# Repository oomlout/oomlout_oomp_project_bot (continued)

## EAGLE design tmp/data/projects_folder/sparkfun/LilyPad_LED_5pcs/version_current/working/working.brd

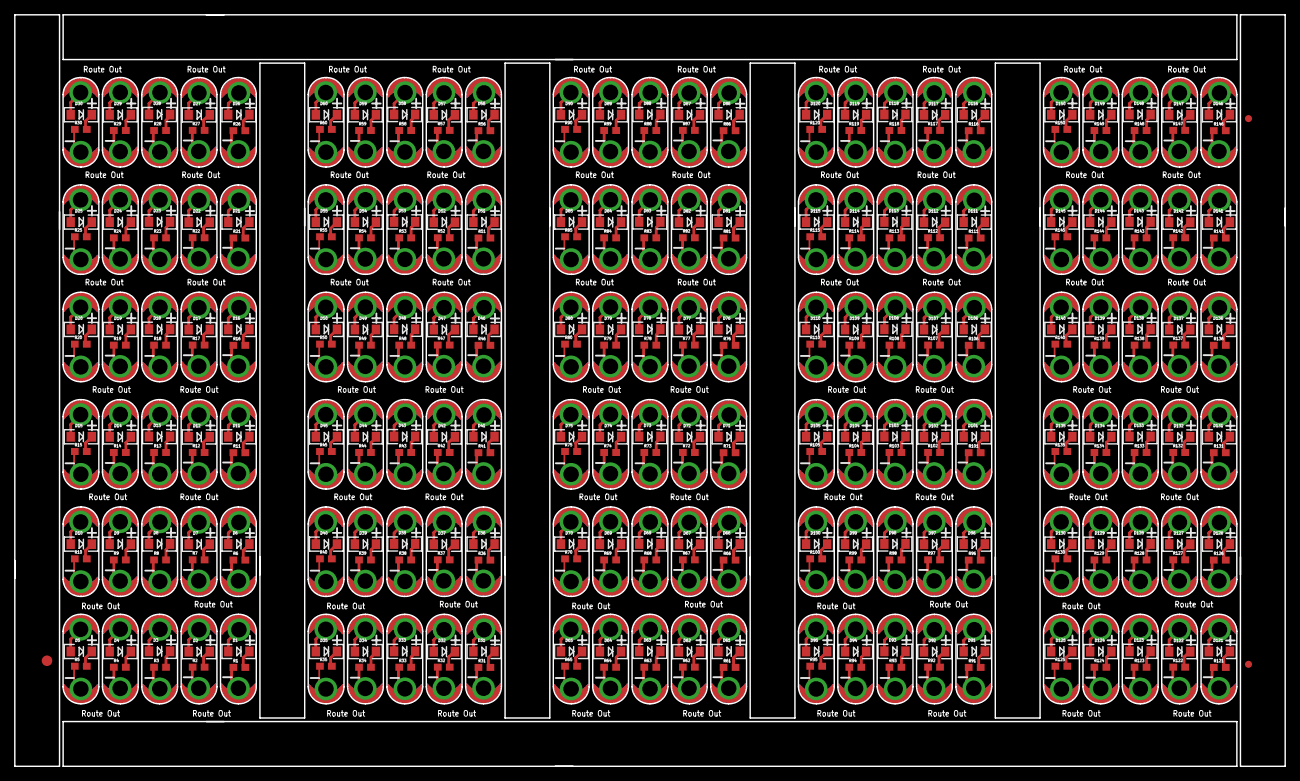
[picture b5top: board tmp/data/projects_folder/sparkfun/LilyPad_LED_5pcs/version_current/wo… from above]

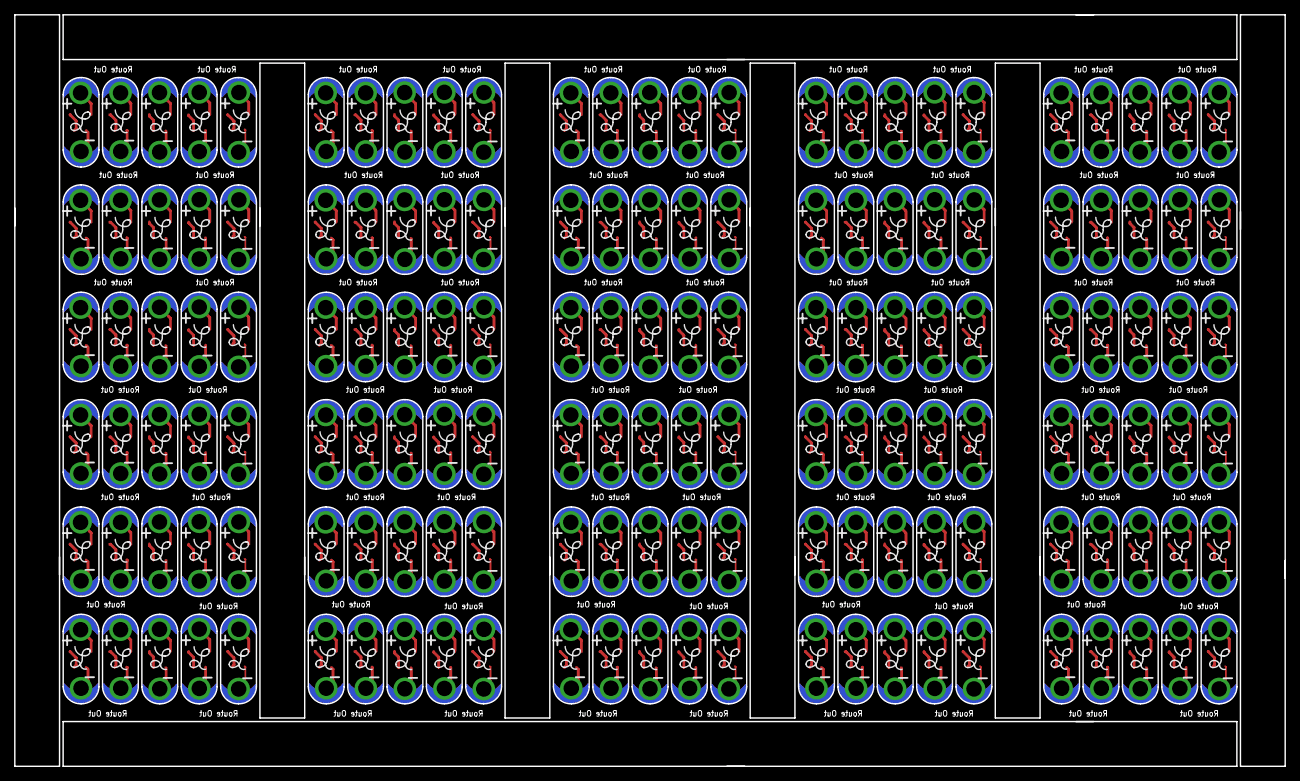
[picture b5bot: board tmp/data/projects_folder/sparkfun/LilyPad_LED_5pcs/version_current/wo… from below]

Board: 2 copper layers, 180.3 x 106.7 mm, 753 parts (150 on the bottom side), 450 nets.

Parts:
D1, D2, D3, D4, D5, D6, D7, D8, D9, D10, D11, D12, D13, D14, D15, D16, D17, D18, D19, D20, D21, D22, D23, D24, D25, D26, D27, D28, D29, D30, D31, D32, D33, D34, D35, D36, D37, D38, D39, D40, D41, D42, D43, D44, D45, D46, D47, D48, D49, D50, D51, D52, D53, D54, D55, D56, D57, D58, D59, D60, D61, D62, D63, D64, D65, D66, D67, D68, D69, D70, D71, D72, D73, D74, D75, D76, D77, D78, D79, D80, D81, D82, D83, D84, D85, D86, D87, D88, D89, D90, D91, D92, D93, D94, D95, D96, D97, D98, D99, D100, D101, D102, D103, D104, D105, D106, D107, D108, D109, D110, D111, D112, D113, D114, D115, D116, D117, D118, D119, D120, D121, D122, D123, D124, D125, D126, D127, D128, D129, D130, D131, D132, D133, D134, D135, D136, D137, D138, D139, D140, D141, D142, D143, D144, D145, D146, D147, D148, D149, D150: WHITE; LED-1206
E$1: FIDUCIAL-1.5X3
E$15, E$16: FIDUCIAL-1X2
LED+1, LED+2, LED+3, LED+4, LED+5, LED+6, LED+7, LED+8, LED+9, LED+10, LED+11, LED+12, LED+13, LED+14, LED+15, LED+16, LED+17, LED+18, LED+19, LED+20, LED+21, LED+22, LED+23, LED+24, LED+25, LED+26, LED+27, LED+28, LED+29, LED+30, LED+31, LED+32, LED+33, LED+34, LED+35, LED+36, LED+37, LED+38, LED+39, LED+40, LED+41, LED+42, LED+43, LED+44, LED+45, LED+46, LED+47, LED+48, LED+49, LED+50, LED+51, LED+52, LED+53, LED+54, LED+55, LED+56, LED+57, LED+58, LED+59, LED+60, LED+61, LED+62, LED+63, LED+64, LED+65, LED+66, LED+67, LED+68, LED+69, LED+70, LED+71, LED+72, LED+73, LED+74, LED+75, LED+76, LED+77, LED+78, LED+79, LED+80, LED+81, LED+82, LED+83, LED+84, LED+85, LED+86, LED+87, LED+88, LED+89, LED+90, LED+91, LED+92, LED+93, LED+94, LED+95, LED+96, LED+97, LED+98, LED+99, LED+100, LED+101, LED+102, LED+103, LED+104, LED+105, LED+106, LED+107, LED+108, LED+109, LED+110, LED+111, LED+112, LED+113, LED+114, LED+115, LED+116, LED+117, LED+118, LED+119, LED+120, LED+121, LED+122, LED+123, LED+124, LED+125, LED+126, LED+127, LED+128, LED+129, LED+130, LED+131, LED+132, LED+133, LED+134, LED+135, LED+136, LED+137, LED+138, LED+139, LED+140, LED+141, LED+142, LED+143, LED+144, LED+145, LED+146, LED+147, LED+148, LED+149, LED+150: SEWTAP6; PETAL-SMALL-2SIDE
LED-1, LED-2, LED-3, LED-4, LED-5, LED-6, LED-7, LED-8, LED-9, LED-10, LED-11, LED-12, LED-13, LED-14, LED-15, LED-16, LED-17, LED-18, LED-19, LED-20, LED-21, LED-22, LED-23, LED-24, LED-25, LED-26, LED-27, LED-28, LED-29, LED-30, LED-31, LED-32, LED-33, LED-34, LED-35, LED-36, LED-37, LED-38, LED-39, LED-40, LED-41, LED-42, LED-43, LED-44, LED-45, LED-46, LED-47, LED-48, LED-49, LED-50, LED-51, LED-52, LED-53, LED-54, LED-55, LED-56, LED-57, LED-58, LED-59, LED-60, LED-61, LED-62, LED-63, LED-64, LED-65, LED-66, LED-67, LED-68, LED-69, LED-70, LED-71, LED-72, LED-73, LED-74, LED-75, LED-76, LED-77, LED-78, LED-79, LED-80, LED-81, LED-82, LED-83, LED-84, LED-85, LED-86, LED-87, LED-88, LED-89, LED-90, LED-91, LED-92, LED-93, LED-94, LED-95, LED-96, LED-97, LED-98, LED-99, LED-100, LED-101, LED-102, LED-103, LED-104, LED-105, LED-106, LED-107, LED-108, LED-109, LED-110, LED-111, LED-112, LED-113, LED-114, LED-115, LED-116, LED-117, LED-118, LED-119, LED-120, LED-121, LED-122, LED-123, LED-124, LED-125, LED-126, LED-127, LED-128, LED-129, LED-130, LED-131, LED-132, LED-133, LED-134, LED-135, LED-136, LED-137, LED-138, LED-139, LED-140, LED-141, LED-142, LED-143, LED-144, LED-145, LED-146, LED-147, LED-148, LED-149, LED-150: SEWTAP6; PETAL-SMALL-2SIDE
R1, R2, R3, R4, R5, R6, R7, R8, R9, R10, R11, R12, R13, R14, R15, R16, R17, R18, R19, R20, R21, R22, R23, R24, R25, R26, R27, R28, R29, R30, R31, R32, R33, R34, R35, R36, R37, R38, R39, R40, R41, R42, R43, R44, R45, R46, R47, R48, R49, R50, R51, R52, R53, R54, R55, R56, R57, R58, R59, R60, R61, R62, R63, R64, R65, R66, R67, R68, R69, R70, R71, R72, R73, R74, R75, R76, R77, R78, R79, R80, R81, R82, R83, R84, R85, R86, R87, R88, R89, R90, R91, R92, R93, R94, R95, R96, R97, R98, R99, R100, R101, R102, R103, R104, R105, R106, R107, R108, R109, R110, R111, R112, R113, R114, R115, R116, R117, R118, R119, R120, R121, R122, R123, R124, R125, R126, R127, R128, R129, R130, R131, R132, R133, R134, R135, R136, R137, R138, R139, R140, R141, R142, R143, R144, R145, R146, R147, R148, R149, R150: 150; 0603-RES
U$1, U$2, U$3, U$4, U$5, U$6, U$7, U$8, U$9, U$10, U$11, U$12, U$13, U$14, U$15, U$16, U$17, U$18, U$19, U$20, U$21, U$22, U$23, U$24, U$25, U$26, U$27, U$28, U$29, U$30, U$31, U$32, U$33, U$34, U$35, U$36, U$37, U$38, U$39, U$40, U$41, U$42, U$43, U$44, U$45, U$46, U$47, U$48, U$49, U$50, U$51, U$52, U$53, U$54, U$55, U$56, U$57, U$58, U$59, U$60, U$61, U$62, U$63, U$64, U$65, U$66, U$67, U$68, U$69, U$70, U$71, U$72, U$73, U$74, U$75, U$76, U$77, U$78, U$79, U$80, U$81, U$82, U$83, U$84, U$85, U$86, U$87, U$88, U$89, U$90, U$91, U$92, U$93, U$94, U$95, U$96, U$97, U$98, U$99, U$100, U$101, U$102, U$103, U$104, U$105, U$106, U$107, U$108, U$109, U$110, U$111, U$112, U$113, U$114, U$115, U$116, U$117, U$118, U$119, U$120, U$121, U$122, U$123, U$124, U$125, U$126, U$127, U$128, U$129, U$130, U$131, U$132, U$133, U$134, U$135, U$136, U$137, U$138, U$139, U$140, U$141, U$142, U$143, U$144, U$145, U$146, U$147, U$148, U$149, U$150: LOGO-L

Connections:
1: D1.A, LED+1.1
2: D1.C, R1.2
3: LED-1.1, R1.1
4: D2.A, LED+2.1
5: D2.C, R2.2
6: LED-2.1, R2.1
7: D3.A, LED+3.1
8: D3.C, R3.2
9: LED-3.1, R3.1
10: D4.A, LED+4.1
11: D4.C, R4.2
12: LED-4.1, R4.1
13: D5.A, LED+5.1
14: D5.C, R5.2
15: LED-5.1, R5.1
16: LED-6.1, R6.1
17: D6.A, LED+6.1
18: D6.C, R6.2
19: D7.A, LED+7.1
20: D7.C, R7.2
21: LED-7.1, R7.1
22: D8.A, LED+8.1
23: D8.C, R8.2
24: LED-8.1, R8.1
25: LED-9.1, R9.1
26: D9.C, R9.2
27: D9.A, LED+9.1
28: D10.A, LED+10.1
29: D10.C, R10.2
30: LED-10.1, R10.1
31: LED-11.1, R11.1
32: D11.A, LED+11.1
33: D11.C, R11.2
34: D12.A, LED+12.1
35: D12.C, R12.2
36: LED-12.1, R12.1
37: D13.A, LED+13.1
38: D13.C, R13.2
39: LED-13.1, R13.1
40: LED-14.1, R14.1
41: D14.C, R14.2
42: D14.A, LED+14.1
43: D15.A, LED+15.1
44: D15.C, R15.2
45: LED-15.1, R15.1
46: LED-16.1, R16.1
47: D16.A, LED+16.1
48: D16.C, R16.2
49: D17.A, LED+17.1
50: D17.C, R17.2
51: LED-17.1, R17.1
52: D18.A, LED+18.1
53: D18.C, R18.2
54: LED-18.1, R18.1
55: LED-19.1, R19.1
56: D19.C, R19.2
57: D19.A, LED+19.1
58: D20.A, LED+20.1
59: D20.C, R20.2
60: LED-20.1, R20.1
61: LED-21.1, R21.1
62: D21.A, LED+21.1
63: D21.C, R21.2
64: D22.A, LED+22.1
65: D22.C, R22.2
66: LED-22.1, R22.1
67: D23.A, LED+23.1
68: D23.C, R23.2
69: LED-23.1, R23.1
70: LED-24.1, R24.1
71: D24.C, R24.2
72: D24.A, LED+24.1
73: D25.A, LED+25.1
74: D25.C, R25.2
75: LED-25.1, R25.1
76: LED-26.1, R26.1
77: D26.A, LED+26.1
78: D26.C, R26.2
79: D27.A, LED+27.1
80: D27.C, R27.2
81: LED-27.1, R27.1
82: D28.A, LED+28.1
83: D28.C, R28.2
84: LED-28.1, R28.1
85: LED-29.1, R29.1
86: D29.C, R29.2
87: D29.A, LED+29.1
88: D30.A, LED+30.1
89: D30.C, R30.2
90: LED-30.1, R30.1
91: LED-31.1, R31.1
92: D31.A, LED+31.1
93: D31.C, R31.2
94: D32.A, LED+32.1
95: D32.C, R32.2
96: LED-32.1, R32.1
97: D33.A, LED+33.1
98: D33.C, R33.2
99: LED-33.1, R33.1
100: LED-34.1, R34.1
101: D34.C, R34.2
102: D34.A, LED+34.1
103: D35.A, LED+35.1
104: D35.C, R35.2
105: LED-35.1, R35.1
106: LED-36.1, R36.1
107: D36.A, LED+36.1
108: D36.C, R36.2
109: D37.A, LED+37.1
110: D37.C, R37.2
111: LED-37.1, R37.1
112: D38.A, LED+38.1
113: D38.C, R38.2
114: LED-38.1, R38.1
115: LED-39.1, R39.1
116: D39.C, R39.2
117: D39.A, LED+39.1
118: D40.A, LED+40.1
119: D40.C, R40.2
120: LED-40.1, R40.1
121: LED-41.1, R41.1
122: D41.A, LED+41.1
123: D41.C, R41.2
124: D42.A, LED+42.1
125: D42.C, R42.2
126: LED-42.1, R42.1
127: D43.A, LED+43.1
128: D43.C, R43.2
129: LED-43.1, R43.1
130: LED-44.1, R44.1
131: D44.C, R44.2
132: D44.A, LED+44.1
133: D45.A, LED+45.1
134: D45.C, R45.2
135: LED-45.1, R45.1
136: LED-46.1, R46.1
137: D46.A, LED+46.1
138: D46.C, R46.2
139: D47.A, LED+47.1
140: D47.C, R47.2
141: LED-47.1, R47.1
142: D48.A, LED+48.1
143: D48.C, R48.2
144: LED-48.1, R48.1
145: LED-49.1, R49.1
146: D49.C, R49.2
147: D49.A, LED+49.1
148: D50.A, LED+50.1
149: D50.C, R50.2
150: LED-50.1, R50.1
151: LED-51.1, R51.1
152: D51.A, LED+51.1
153: D51.C, R51.2
154: D52.A, LED+52.1
155: D52.C, R52.2
156: LED-52.1, R52.1
157: D53.A, LED+53.1
158: D53.C, R53.2
159: LED-53.1, R53.1
160: LED-54.1, R54.1
161: D54.C, R54.2
162: D54.A, LED+54.1
163: D55.A, LED+55.1
164: D55.C, R55.2
165: LED-55.1, R55.1
166: LED-56.1, R56.1
167: D56.A, LED+56.1
168: D56.C, R56.2
169: D57.A, LED+57.1
170: D57.C, R57.2
171: LED-57.1, R57.1
172: D58.A, LED+58.1
173: D58.C, R58.2
174: LED-58.1, R58.1
175: LED-59.1, R59.1
176: D59.C, R59.2
177: D59.A, LED+59.1
178: D60.A, LED+60.1
179: D60.C, R60.2
180: LED-60.1, R60.1
181: LED-61.1, R61.1
182: D61.A, LED+61.1
183: D61.C, R61.2
184: D62.A, LED+62.1
185: D62.C, R62.2
186: LED-62.1, R62.1
187: D63.A, LED+63.1
188: D63.C, R63.2
189: LED-63.1, R63.1
190: LED-64.1, R64.1
191: D64.C, R64.2
192: D64.A, LED+64.1
193: D65.A, LED+65.1
194: D65.C, R65.2
195: LED-65.1, R65.1
196: LED-66.1, R66.1
197: D66.A, LED+66.1
198: D66.C, R66.2
199: D67.A, LED+67.1
200: D67.C, R67.2
201: LED-67.1, R67.1
202: D68.A, LED+68.1
203: D68.C, R68.2
204: LED-68.1, R68.1
205: LED-69.1, R69.1
206: D69.C, R69.2
207: D69.A, LED+69.1
208: D70.A, LED+70.1
209: D70.C, R70.2
210: LED-70.1, R70.1
211: LED-71.1, R71.1
212: D71.A, LED+71.1
213: D71.C, R71.2
214: D72.A, LED+72.1
215: D72.C, R72.2
216: LED-72.1, R72.1
217: D73.A, LED+73.1
218: D73.C, R73.2
219: LED-73.1, R73.1
220: LED-74.1, R74.1
221: D74.C, R74.2
222: D74.A, LED+74.1
223: D75.A, LED+75.1
224: D75.C, R75.2
225: LED-75.1, R75.1
226: LED-76.1, R76.1
227: D76.A, LED+76.1
228: D76.C, R76.2
229: D77.A, LED+77.1
230: D77.C, R77.2
231: LED-77.1, R77.1
232: D78.A, LED+78.1
233: D78.C, R78.2
234: LED-78.1, R78.1
235: LED-79.1, R79.1
236: D79.C, R79.2
237: D79.A, LED+79.1
238: D80.A, LED+80.1
239: D80.C, R80.2
240: LED-80.1, R80.1
241: LED-81.1, R81.1
242: D81.A, LED+81.1
243: D81.C, R81.2
244: D82.A, LED+82.1
245: D82.C, R82.2
246: LED-82.1, R82.1
247: D83.A, LED+83.1
248: D83.C, R83.2
249: LED-83.1, R83.1
250: LED-84.1, R84.1
251: D84.C, R84.2
252: D84.A, LED+84.1
253: D85.A, LED+85.1
254: D85.C, R85.2
255: LED-85.1, R85.1
256: LED-86.1, R86.1
257: D86.A, LED+86.1
258: D86.C, R86.2
259: D87.A, LED+87.1
260: D87.C, R87.2
261: LED-87.1, R87.1
262: D88.A, LED+88.1
263: D88.C, R88.2
264: LED-88.1, R88.1
265: LED-89.1, R89.1
266: D89.C, R89.2
267: D89.A, LED+89.1
268: D90.A, LED+90.1
269: D90.C, R90.2
270: LED-90.1, R90.1
271: LED-91.1, R91.1
272: D91.A, LED+91.1
273: D91.C, R91.2
274: D92.A, LED+92.1
275: D92.C, R92.2
276: LED-92.1, R92.1
277: D93.A, LED+93.1
278: D93.C, R93.2
279: LED-93.1, R93.1
280: LED-94.1, R94.1
281: D94.C, R94.2
282: D94.A, LED+94.1
283: D95.A, LED+95.1
284: D95.C, R95.2
285: LED-95.1, R95.1
286: LED-96.1, R96.1
287: D96.A, LED+96.1
288: D96.C, R96.2
289: D97.A, LED+97.1
290: D97.C, R97.2
291: LED-97.1, R97.1
292: D98.A, LED+98.1
293: D98.C, R98.2
294: LED-98.1, R98.1
295: LED-99.1, R99.1
296: D99.C, R99.2
297: D99.A, LED+99.1
298: D100.A, LED+100.1
299: D100.C, R100.2
300: LED-100.1, R100.1
301: LED-101.1, R101.1
302: D101.A, LED+101.1
303: D101.C, R101.2
304: D102.A, LED+102.1
305: D102.C, R102.2
306: LED-102.1, R102.1
307: D103.A, LED+103.1
308: D103.C, R103.2
309: LED-103.1, R103.1
310: LED-104.1, R104.1
311: D104.C, R104.2
312: D104.A, LED+104.1
313: D105.A, LED+105.1
314: D105.C, R105.2
315: LED-105.1, R105.1
316: LED-106.1, R106.1
317: D106.A, LED+106.1
318: D106.C, R106.2
319: D107.A, LED+107.1
320: D107.C, R107.2
321: LED-107.1, R107.1
322: D108.A, LED+108.1
323: D108.C, R108.2
324: LED-108.1, R108.1
325: LED-109.1, R109.1
326: D109.C, R109.2
327: D109.A, LED+109.1
328: D110.A, LED+110.1
329: D110.C, R110.2
330: LED-110.1, R110.1
331: LED-111.1, R111.1
332: D111.A, LED+111.1
333: D111.C, R111.2
334: D112.A, LED+112.1
335: D112.C, R112.2
336: LED-112.1, R112.1
337: D113.A, LED+113.1
338: D113.C, R113.2
339: LED-113.1, R113.1
340: LED-114.1, R114.1
341: D114.C, R114.2
342: D114.A, LED+114.1
343: D115.A, LED+115.1
344: D115.C, R115.2
345: LED-115.1, R115.1
346: LED-116.1, R116.1
347: D116.A, LED+116.1
348: D116.C, R116.2
349: D117.A, LED+117.1
350: D117.C, R117.2
351: LED-117.1, R117.1
352: D118.A, LED+118.1
353: D118.C, R118.2
354: LED-118.1, R118.1
355: LED-119.1, R119.1
356: D119.C, R119.2
357: D119.A, LED+119.1
358: D120.A, LED+120.1
359: D120.C, R120.2
360: LED-120.1, R120.1
361: LED-121.1, R121.1
362: D121.A, LED+121.1
363: D121.C, R121.2
364: D122.A, LED+122.1
365: D122.C, R122.2
366: LED-122.1, R122.1
367: D123.A, LED+123.1
368: D123.C, R123.2
369: LED-123.1, R123.1
370: LED-124.1, R124.1
371: D124.C, R124.2
372: D124.A, LED+124.1
373: D125.A, LED+125.1
374: D125.C, R125.2
375: LED-125.1, R125.1
376: LED-126.1, R126.1
377: D126.A, LED+126.1
378: D126.C, R126.2
379: D127.A, LED+127.1
380: D127.C, R127.2
381: LED-127.1, R127.1
382: D128.A, LED+128.1
383: D128.C, R128.2
384: LED-128.1, R128.1
385: LED-129.1, R129.1
386: D129.C, R129.2
387: D129.A, LED+129.1
388: D130.A, LED+130.1
389: D130.C, R130.2
390: LED-130.1, R130.1
391: LED-131.1, R131.1
392: D131.A, LED+131.1
393: D131.C, R131.2
394: D132.A, LED+132.1
395: D132.C, R132.2
396: LED-132.1, R132.1
397: D133.A, LED+133.1
398: D133.C, R133.2
399: LED-133.1, R133.1
400: LED-134.1, R134.1
401: D134.C, R134.2
402: D134.A, LED+134.1
403: D135.A, LED+135.1
404: D135.C, R135.2
405: LED-135.1, R135.1
406: LED-136.1, R136.1
407: D136.A, LED+136.1
408: D136.C, R136.2
409: D137.A, LED+137.1
410: D137.C, R137.2
411: LED-137.1, R137.1
412: D138.A, LED+138.1
413: D138.C, R138.2
414: LED-138.1, R138.1
415: LED-139.1, R139.1
416: D139.C, R139.2
417: D139.A, LED+139.1
418: D140.A, LED+140.1
419: D140.C, R140.2
420: LED-140.1, R140.1
421: LED-141.1, R141.1
422: D141.A, LED+141.1
423: D141.C, R141.2
424: D142.A, LED+142.1
425: D142.C, R142.2
426: LED-142.1, R142.1
427: D143.A, LED+143.1
428: D143.C, R143.2
429: LED-143.1, R143.1
430: LED-144.1, R144.1
431: D144.C, R144.2
432: D144.A, LED+144.1
433: D145.A, LED+145.1
434: D145.C, R145.2
435: LED-145.1, R145.1
436: LED-146.1, R146.1
437: D146.A, LED+146.1
438: D146.C, R146.2
439: D147.A, LED+147.1
440: D147.C, R147.2
441: LED-147.1, R147.1
442: D148.A, LED+148.1
443: D148.C, R148.2
444: LED-148.1, R148.1
445: LED-149.1, R149.1
446: D149.C, R149.2
447: D149.A, LED+149.1
448: D150.A, LED+150.1
449: D150.C, R150.2
450: LED-150.1, R150.1
